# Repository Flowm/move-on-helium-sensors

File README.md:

# MOVE-ON Helium Sensors
Sensors subsystem for the MOVE-ON Helium high-altitude balloon mission.

A detailed system description can be found in .

## Interfaces
### Micro USB
The output from Micro USB can be read with the following command (MacOS):
```
picocom -b 115200 /dev/tty.usbmodem1453
```
(`usbmodem1453` needs to be adjusted on your system)

## Setup
### Requirements
- GNU Arm Embedded Toolchain
- mbed-cli
- stlink

### MacOS
```
brew cask install gcc-arm-embedded
brew install stlink openocd direnv
sudo easy_install pip
pip install virtualenv

echo 'eval "$(direnv hook bash)"' >> ~/.bashrc
echo 'eval "$(direnv hook zsh)"' >> ~/.zshrc
```

If `pip install` does not work try it with the parameter `--user python`.

### Linux
```
sudo apt install gcc-arm-none-eabi openocd
sudo apt install python-pip python-dev build-essential direnv
pip install virtualenv

echo 'eval "$(direnv hook bash)"' >> ~/.bashrc
echo 'eval "$(direnv hook zsh)"' >> ~/.zshrc
```

### Mbed-cli
New shell in project directory:
```
direnv allow
pip install mbed-cli
```

## Development
### Compile
In `src` dir:
```
make
```

### Developing in SW4STM32 (Eclipse)
1. `mbed-cli export -i sw4stm32 --profile config/develop.json`
2. `File` -> `Open Projects from File System` (In Eclipse)
3. Choose the `move-on-helium-sensors` project.
4. Remember to regenerate the project files everytime you add a new library with `mbed-cli add ...`.

## Reference
### Build targets
From the `src` directory:

| Command                 | Description                                             |
| ----------------------- | ------------------------------------------------------- |
| make build (default)    | Generate toplevel makefile and build project sources    |
| make clean              | Remove build artifacts and toplevel makefile            |
| make flash              | Upload firmware to locally attached uC with st-flash    |
| make rflash             | Upload firmware to uC attached to remote ci host        |
| make rtail              | Tail serial output from uC attached to remote ci host   |
| make deploy             | Combines rflash and rtail                               |

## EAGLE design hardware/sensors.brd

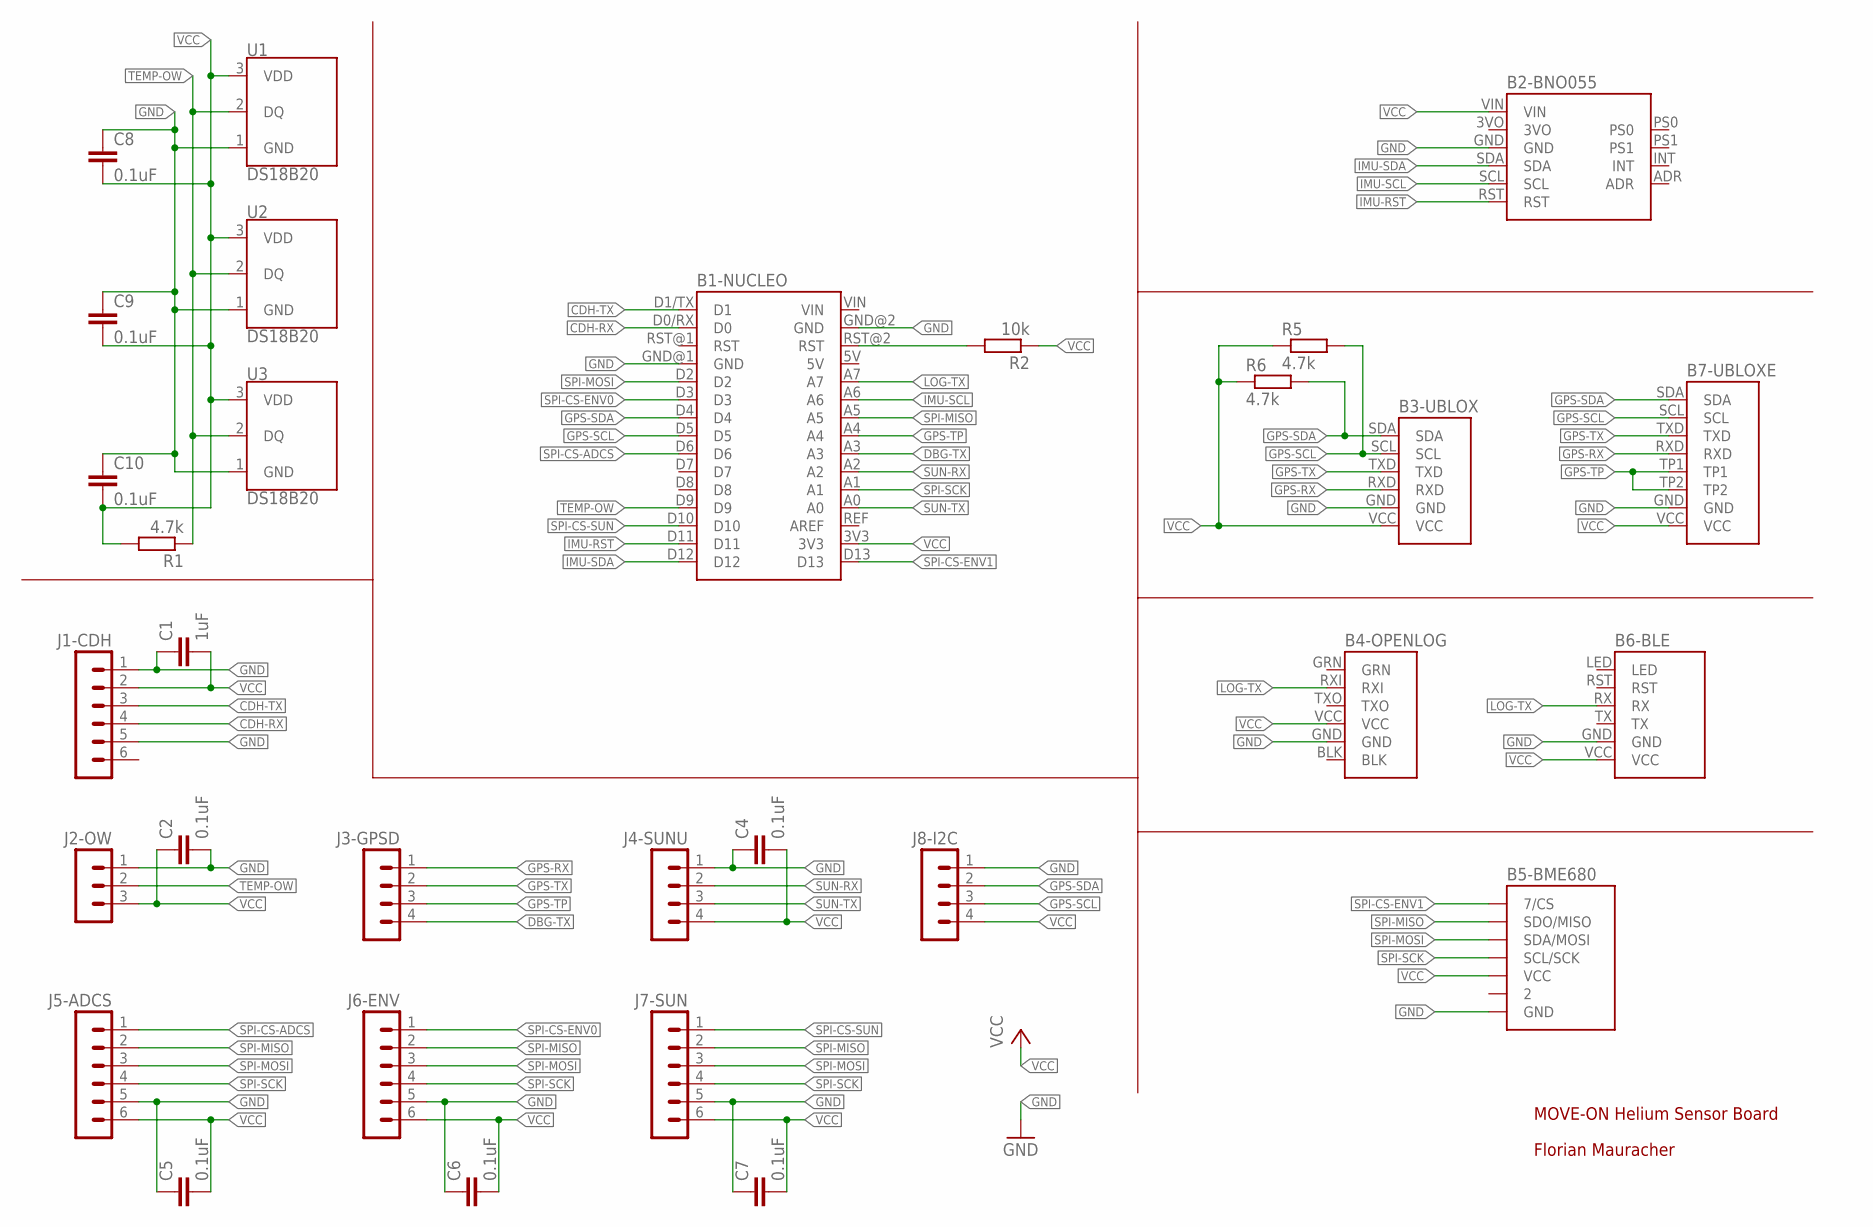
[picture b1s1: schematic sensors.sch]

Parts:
B1-NUCLEO: NUCLEO-32BO; NUCLEO-32
B2-BNO055: BOSCH-BNO055BO; BOSCH-BNO055
B3-UBLOX: UPUTRONICS-UBLOX-PICOBO; UPUTRONICS-UBLOX-PICO
B4-OPENLOG: SPARKFUN-OPENLOGBO; SPARKFUN-OPENLOG
B5-BME680: WATTEROT-BME680BO; WATTEROT-BME680
B6-BLE: HUAMAO-HM-11BO; HUAMAO-HM-11
B7-UBLOXE: UPUTRONICS-UBLOX-M8Q
C1: 1uF; C2012
C2, C4, C5, C6, C7, C8, C9, C10: 0.1uF; C2012
J1-CDH, J5-ADCS, J6-ENV, J7-SUN: 90136-106; 90136-1?06
J2-OW: 90136-103; 90136-1?03
J3-GPSD, J4-SUNU, J8-I2C: 90136-104; 90136-1?04
R1, R5, R6: 4.7k; R2012
R2: 10k; R2012
U1, U2, U3: DS18B20; TO-92-AMMO

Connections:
5V: B1-NUCLEO.5V
CDH-RX: B1-NUCLEO.D0/RX (D0), J1-CDH.4
CDH-TX: B1-NUCLEO.D1/TX (D1), J1-CDH.3
DBG-TX: B1-NUCLEO.A3, J3-GPSD.4
GND: B1-NUCLEO.GND@1 (GND), B1-NUCLEO.GND@2 (GND), B2-BNO055.GND, B3-UBLOX.GND, B4-OPENLOG.GND, B5-BME680.GND, B6-BLE.GND, B7-UBLOXE.GND, C1.1, C2.2, C4.1, C5.1, C6.1, C7.1, C8.1, C9.1, C10.1, J1-CDH.1, J1-CDH.5, J2-OW.1, J4-SUNU.1, J5-ADCS.5, J6-ENV.5, J7-SUN.5, J8-I2C.1, U1.1 (GND), U2.1 (GND), U3.1 (GND); also elsewhere on the board
GPS-RX: B3-UBLOX.RXD, B7-UBLOXE.RXD, J3-GPSD.1
GPS-SCL: B1-NUCLEO.D5, B3-UBLOX.SCL, B7-UBLOXE.SCL, J8-I2C.3, R5.2
GPS-SDA: B1-NUCLEO.D4, B3-UBLOX.SDA, B7-UBLOXE.SDA, J8-I2C.2, R6.2
GPS-TP: B1-NUCLEO.A4, B7-UBLOXE.TP1, B7-UBLOXE.TP2, J3-GPSD.3
GPS-TX: B3-UBLOX.TXD, B7-UBLOXE.TXD, J3-GPSD.2
GRN: B4-OPENLOG.GRN
IMU-RST: B1-NUCLEO.D11, B2-BNO055.RST
IMU-SCL: B1-NUCLEO.A6, B2-BNO055.SCL
IMU-SDA: B1-NUCLEO.D12, B2-BNO055.SDA
LOG-TX: B1-NUCLEO.A7, B4-OPENLOG.RXI, B6-BLE.RX
NUC-RST: B1-NUCLEO.RST@2 (RST), R2.2
SPI-CS-ADCS: B1-NUCLEO.D6, J5-ADCS.1
SPI-CS-ENV0: B1-NUCLEO.D3, J6-ENV.1
SPI-CS-ENV1: B1-NUCLEO.D13, B5-BME680.CS (7/CS)
SPI-CS-SUN: B1-NUCLEO.D10, J7-SUN.1
SPI-MISO: B1-NUCLEO.A5, B5-BME680.SDO/MISO, J5-ADCS.2, J6-ENV.2, J7-SUN.2
SPI-MOSI: B1-NUCLEO.D2, B5-BME680.SDA/MOSI, J5-ADCS.3, J6-ENV.3, J7-SUN.3
SPI-SCK: B1-NUCLEO.A1, B5-BME680.SCL/SCK, J5-ADCS.4, J6-ENV.4, J7-SUN.4
SUN-RX: B1-NUCLEO.A2, J4-SUNU.2
SUN-TX: B1-NUCLEO.A0, J4-SUNU.3
TEMP-OW: B1-NUCLEO.D9, J2-OW.2, R1.1, U1.2 (DQ), U2.2 (DQ), U3.2 (DQ)
VCC: B1-NUCLEO.3V3, B2-BNO055.VIN, B3-UBLOX.VCC, B4-OPENLOG.VCC, B5-BME680.VCC, B6-BLE.VCC, B7-UBLOXE.VCC, C1.2, C2.1, C4.2, C5.2, C6.2, C7.2, C8.2, C9.2, C10.2, J1-CDH.2, J2-OW.3, J4-SUNU.4, J5-ADCS.6, J6-ENV.6, J7-SUN.6, J8-I2C.4, R1.2, R2.1, R5.1, R6.1, U1.3 (VDD), U2.3 (VDD), U3.3 (VDD); also elsewhere on the board
VIN: B1-NUCLEO.VIN

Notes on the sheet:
MOVE-ON Helium Sensor Board
Florian Mauracher

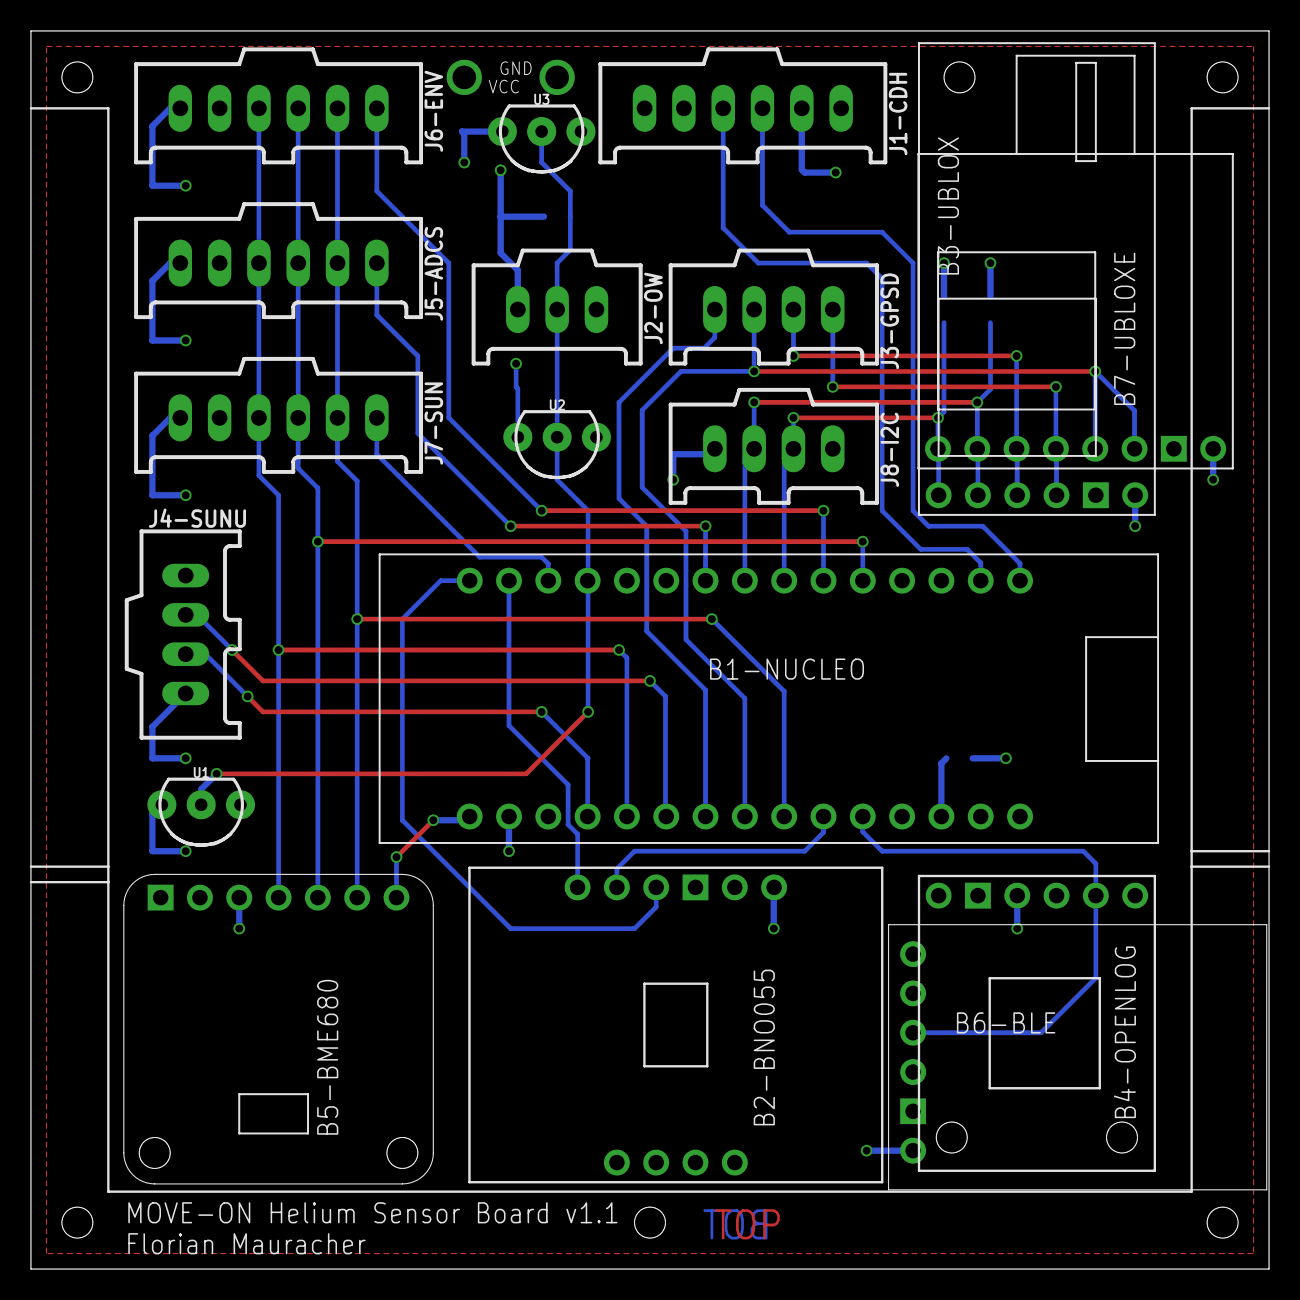
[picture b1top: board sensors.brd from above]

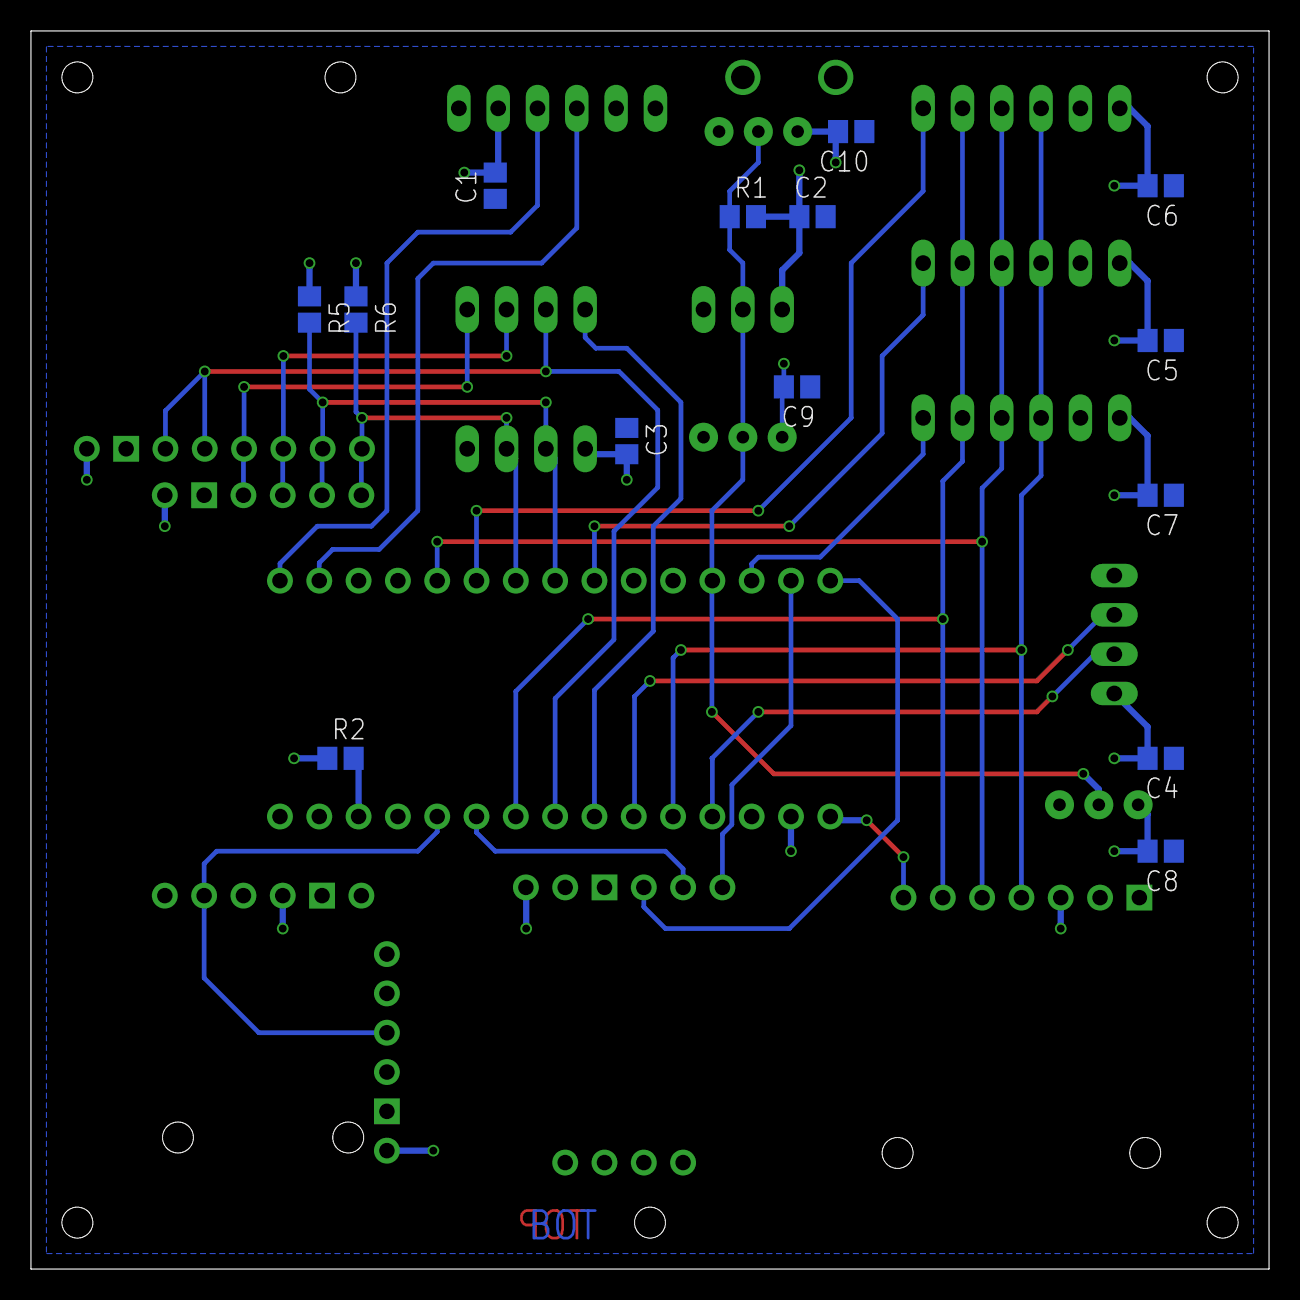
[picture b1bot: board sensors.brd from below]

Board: 2 copper layers, 80.0 x 80.0 mm, 32 parts (14 on the bottom side), 25 nets.

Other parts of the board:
C3: 0.1uF; C2012

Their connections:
GND: C3.1; also elsewhere on the board
VCC: C3.2; also elsewhere on the board

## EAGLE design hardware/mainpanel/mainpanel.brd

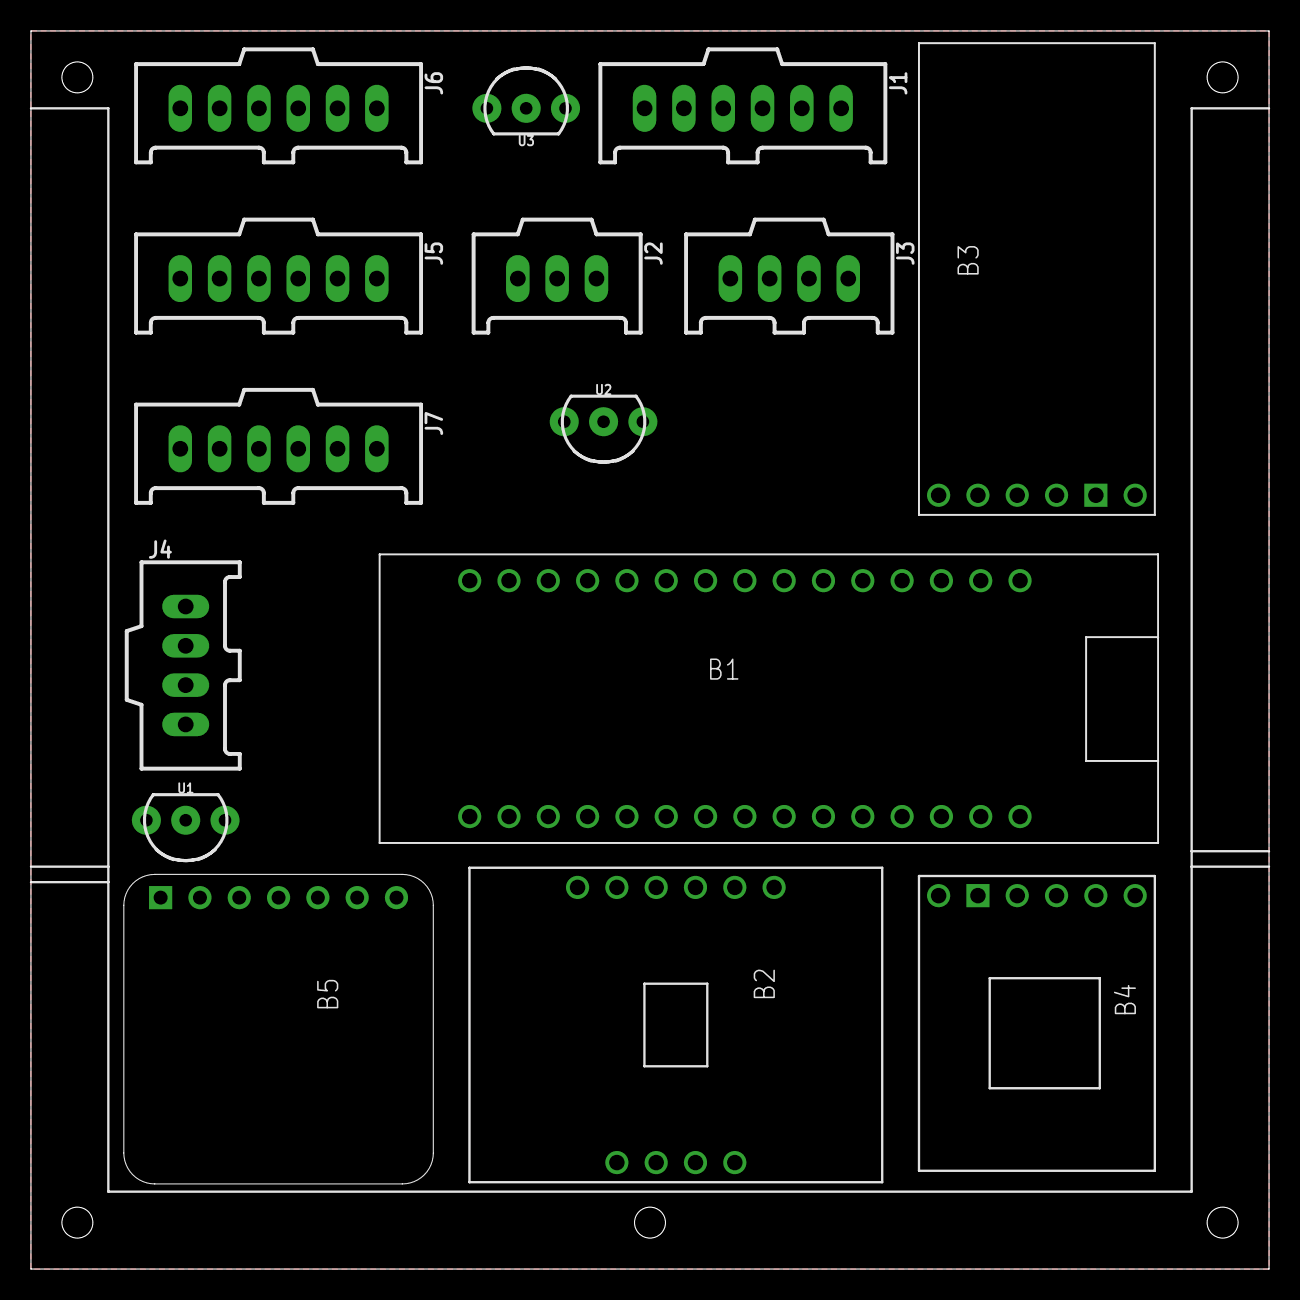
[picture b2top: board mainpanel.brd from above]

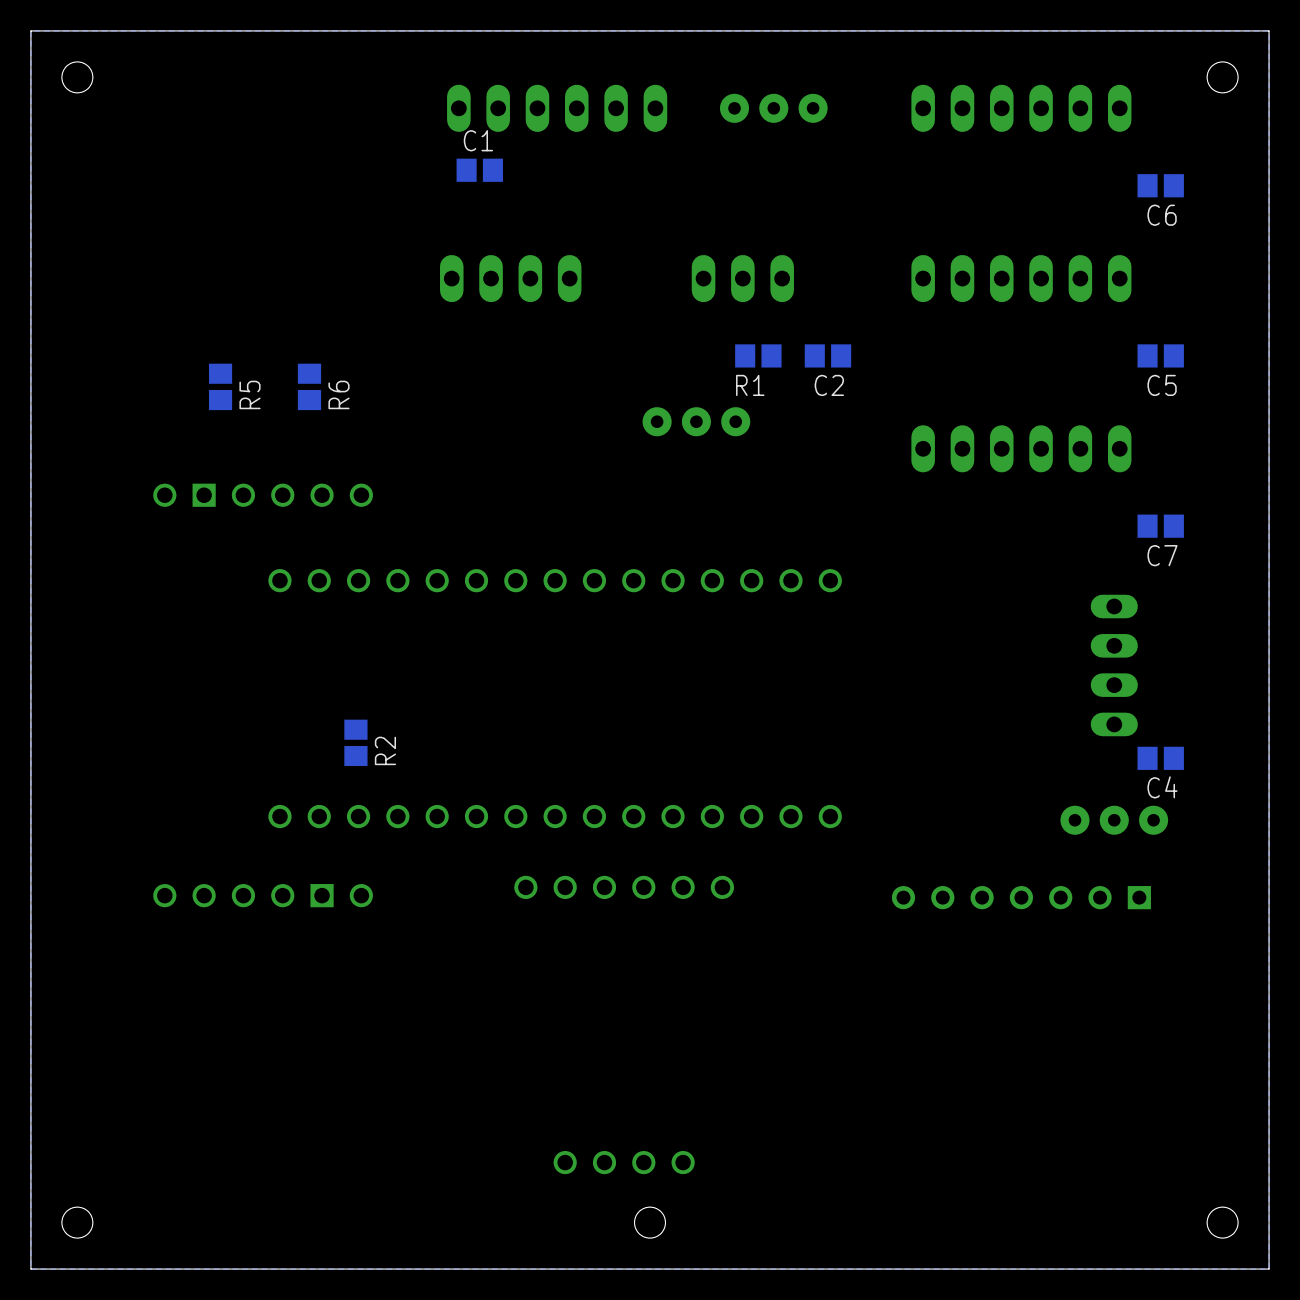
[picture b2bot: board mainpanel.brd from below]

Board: 2 copper layers, 80.0 x 80.0 mm, 25 parts (10 on the bottom side), 25 nets, no tracks yet.

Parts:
B1: NUCLEO-32
B2: BNO055; BOSCH-BNO055
B3: UBLOX; UPUTRONICS-UBLOX-PICO
B4: OPENLOG; SPARKFUN-OPENLOG
B5: BME680; WATTEROT-BME680
C1: 0.2uF; C2012
C2, C4, C5, C6, C7: 0.1uF; C2012
J1: CDH; 90136-1?06
J2: OW; 90136-1?03
J3: DBG; 90136-1?04
J4: SUN-UART; 90136-1?04
J5: ADCS; 90136-1?06
J6: ENV; 90136-1?06
J7: SUN; 90136-1?06
R1, R2, R5, R6: 4.7k; R2012
U1, U2, U3: DS18B20; TO-92-AMMO

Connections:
CDH-RX: B1.D0/RX, J1.4
CDH-TX: B1.D1/TX, J1.3
DBG-RX: B1.A4, J3.3
DBG-TX: B1.A3, J3.4
GND: B1.GND@1, B1.GND@2, B2.GND, B3.GND, B4.GND, B5.GND, C1.1, C2.1, C4.1, C5.1, C6.1, C7.1, J1.1, J1.5, J2.1, J4.1, J5.4, J6.4, J7.4, U1.1, U2.1, U3.1
GPS-RX: B3.RXD, J3.1
GPS-SCL: B1.D5, B3.SCL, R5.2
GPS-SDA: B1.D4, B3.SDA, R6.2
GPS-TX: B3.TXD, J3.2
IMU-RST: B1.D11, B2.RST
IMU-SCL: B1.A6, B2.SCL
IMU-SDA: B1.D12, B2.SDA
LOG-UART: B1.A7, B4.RXI
NUC-RST: B1.RST@2, R2.2
SPI-CS-ADCS: B1.D6, J5.1
SPI-CS-ENO: B1.D13, B5.CS
SPI-CS-ENV: B1.D3, J6.1
SPI-CS-SUN: B1.D10, J7.1
SPI-MISO: B1.A5, B5.SDO/MISO, J5.2, J6.2, J7.2
SPI-MOSI: B1.D2, B5.SDA/MOSI, J5.3, J6.3, J7.3
SPI-SCK: B1.A1, B5.SCL/SCK, J5.5, J6.5, J7.5
SUN-RX: B1.A2, J4.2
SUN-TX: B1.A0, J4.3
TEMP-OW: B1.D9, J2.2, R1.2, U1.2, U2.2, U3.2
VCC: B1.3V3, B2.VIN, B3.VCC, B4.VCC, B5.VCC, C1.2, C2.2, C4.2, C5.2, C6.2, C7.2, J1.2, J2.3, J4.4, J5.6, J6.6, J7.6, R1.1, R2.1, R5.1, R6.1, U1.3, U2.3, U3.3

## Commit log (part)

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2017-12-12 Init mbed project
2017-12-12 Add direnv and editorconfig
2017-12-12 Add basic main.cpp with pin configuration
2017-12-12 Wrap mbed build and flash in an ugly makefile
2017-12-12 Basic I2C and SPI sensor test
2017-12-14 Move port definition to sensor class
2017-12-15 Update mbed config file
2017-12-16 Implemented the MPC320X ADC Driver.
2017-12-17 Import default mbed-os build profile
2017-12-17 Switch to C++17 and C11
    Disable strict-aliasing and sized-deallocation to get rid of compiler
    warnings for mbed-os.
2017-12-20 Add circleci config
2017-12-21 Add gitlab-ci config
2017-12-21 Configure serial console with stty
2018-01-07 Explain makefile targets in readme
2018-01-07 Only install required dependencies in docker container
2018-01-12 Add basic BNO055 class testing chipid
2018-01-15 Remove unnecessary command buffer.
    Also change `rxGetLastChar()` to `getc` to prevent a buffer overflow.
2018-01-15 Update modeserial library to my repo.
    Added support for our Nucleo board. This allows for seamless setup
    of the projects for new members.
2018-01-15 Add the MODSERIAL Library to the project.
2018-01-15 Add CDH data request handling.
    Currently responds with a dummy packets with the opcode mirrorred in
    the status field.
2018-01-15 Process CDH commands in an event queue.
2018-01-15 Fix includes.
2018-01-15 Update modserial version to resolve build error.
2018-01-16 Update modserial lib to the correct HG commit.
2018-01-17 Implement BME680 sensor readout
2018-01-21 Remove sudo from pip cmd
    https://stackoverflow.com/questions/21055859/what-are-the-risks-of-running-sudo-pip
2018-01-22 Missing semicolon in the zsh/bash rc's.
2018-01-22 Fix quotations marks and redirects (to enable auto-merge)
2018-01-23 Copy data while handling CDH commands.
2018-01-23 Cleanup BME680 update func
2018-01-23 Describe bme680 thread configuration in comment
2018-01-23 Add data storage class
2018-01-23 Move BME680 lib to lib folder
2018-01-24 Only start sensor thread if sensor setup is successful
2018-01-25 Add Apache v2 LICENSE
2018-01-28 Add copying the data to the Storage
    This includes debugging output and is probably not the final version ... ;)
2018-01-28 Comment some stuff, learnt from the EPS team
2018-01-29 Remove aliases for vector attributes
    H, R, P are not necessary as aliases for X, Y, Z and are removed for clarity
2018-01-29 Remove unused variable, add implicit return to avoid compiler warning, change mapping between lib and storage
2018-01-29 Justify comment and improve formatting
2018-01-29 Make output consistent to official output
    Commented code tends to stay, or might be reused in the Sensors::log() function, so lets make it pretty.
2018-01-29 Add gyroscope and accelerometer temperatures to regular sensor readouts
2018-01-30 Add DS1820 library.
2018-01-30 Dont unlock before printing everything.
2018-01-30 Fix include.
2018-01-30 Review comments.
2018-01-30 Change DS18B20 lib to my fork. Fixes compiler warnings.
2018-01-30 WIP : Add DS1820 lib
2018-01-31 Adds Checksum class with sw and hw implementations.
    Currenntly using the software version because the hardware version
    doesnt seem to work.
2018-01-31 Influxdb line format for direct import.
2018-01-31 Add resetting sensor if selected values are zero, correct RESET pin
2018-02-01 Add mbed-cli deploy as first build step and ignore deployed libs
2018-02-01 Use mqttserial for shared serial access
2018-02-01 Wrap pyserial for serial port access
2018-02-01 Remove non-threadsafe debugging output
2018-02-01 Remove unused variables, move local variables to header file
2018-02-07 Copy datasructure to unlock it before printing over serial
2018-02-07 Move Storage and SensorThread classes to lib folder
2018-02-07 Update BME680 lib to support negative temperatures
2018-02-08 Wait for sensor threads to start and gather inital data
2018-02-14 Remove GCC version restriction.
2018-02-14 Create pinmap documenting all port assignments
2018-02-14 Implement review feedback
    - Rename bme680 chip select pin
    - Pass BNO055 reset pin from sensors class
2018-02-14 Create retention policy for influxdb
2018-02-14 Add short readme for grafana setup
2018-02-15 Add connectors
2018-02-15 Create eagle project
2018-02-15 Add DS18B20 sensors
2018-02-15 Disconnect pin 6 to cdh
2018-02-15 Add more connectors
2018-02-15 Use 0.1uF caps on all vcc/gnd lines
2018-02-15 Move parts on sch
2018-02-15 Move components
2018-02-15 Move components and add 3rd DS18B20
2018-02-15 Add brd
2018-02-15 Set rst pin to vcc
2018-02-15 Move stuff
2018-02-15 Add BNO055 and connections
2018-02-15 Remove trestrict again
2018-02-15 Implement feedback
    - BNO055 RST line
    - Del BNO055 pullups
    - 3 pin hdr for OW sensors
2018-02-15 Move some wires
2018-02-15 Switch to multi-cb dru again
2018-02-15 Add info to silkscreen
2018-02-15 Add caps for onewire sensors
2018-02-15 Update groundplane dimensions and change caps
2018-02-15 Add trestrict for autorouter
2018-02-15 Update lib
2018-02-15 Add trestrict around vcc pads for connection through cap
2018-02-15 Add power connections
2018-02-15 Update spi connectors
2018-02-15 Remove groundplane around gps
2018-02-15 Update pin names to match sw
2018-02-23 Ignore the debug directory for mbed make file generation.
    This prevents multiple inclusion errors and allows for simultaneous
    compilation with eclipse and make.
2018-02-23 Add deploy stage for rpi software
2018-02-23 Move deploy steps from makefile to gitlab ci config
2018-02-23 Add service for ser2mqttCDH.py
2018-02-23 Force reset the repo when deploying to rpi
2018-02-23 Support different topics in mqttserial
2018-02-23 Add timer to measure mutex lock delay
2018-02-23 Calculate sleep time depending on elapsed time
2018-02-23 Remove uC reset from ciflash target
2018-03-01 adapted to changes in stats output (move-on_helium 07653fc)
2018-03-01 Wrap mqtt client in MqttBroker class
2018-03-01 Added CDH grafana publish
2018-03-01 Add telegraf config for cdh and power
2018-03-01 Added ser2mqtt_power.py and moved mqtt scripts in shared dir
2018-03-01 Rename CDH topic in telegraf
2018-03-01 Mirror data to second influxdb
2018-03-01 Install nucleo reset script for every user
2018-03-01 Rename telegraf config file
2018-03-01 added eps output to ser2mqtt_cdh.py
2018-03-07 Increase baudrate of sensors serial
2018-03-07 Start with GPS Implementation.
    * Read data over I2C
    * Basic sanity checks for the data because the lenght field is not
    valid.
2018-03-07 Add note for the hack that works for reading GPS.
    Also attempt to add files to mbedignore and fail.
2018-03-07 Add a mutex to the serial class to prevent printf's getting Garbled.
    Also sets a default baudrate for the new serial class.
    Fix sentence name typo.
2018-03-07 WIP : Improvements to GPS.
2018-03-07 Update location only if we have a valid fix.
2018-03-07 Add minmea lib.
2018-03-07 Makefile hack to remove examples and test from the minmea lib.
    These files caused a compilation faliure.
2018-03-07 Parse valid time when fix is not valid yet.
2018-03-07 Use mbed lib instead of git submodule for BME680
2018-03-07 Fix build and update gitignore
2018-03-07 Change order of data prints
2018-03-08 Use adcs spi cs for env sensor testing
2018-03-08 Serialize serial access across threads
    - Use RawSerial for an interrupt safe printf implementation
    - Lock serial port manually before output
2018-03-12 Fix system stats print
2018-03-12 Add Sidepanel class
2018-03-14 Print mbed memory stats when macro is enabled in config
2018-03-14 Switch Sidepanel mode on startup
2018-03-14 Increase SPI speed
2018-03-14 Prune adcs_software datastructures
2018-03-14 Verify Sidepanel data checksum
2018-03-14 Store sidepanel data in shared structure
2018-03-14 Reset BME680 when no more data is processed
2018-03-14 Parameterize initial crc value
2018-03-14 Lock serial when warning about failed Sidepanel communication
2018-03-15 Add system architecture diagramm
2018-03-19 Add baudrate to README
2018-03-19 Comment TEMP_GYRO everywhere (Storage struct, filling, printing)
    It is still queried by the used BNO055 library though.
2018-03-20 Merge the two IMU reset types into one
    Before it was split into resets where only temperatures show invalid value (104 degrees) and where all sensors show zeroes. Now this is combined into one counter, but it can still be determined which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
2018-03-20 Make sure thread update rate is matched by deducting iteration time
2018-03-20 Add debug printf to thread sleep times
2018-03-22 Move storage and logger references to SensorThread base class
2018-03-23 Update influxdb to public url
2018-03-23 Move gps script and fix title
2018-03-23 Add print for TOSS data
2018-03-23 Implement TOSS sensor readout over spi
2018-03-23 Change comment for speed units.
2018-03-23 Parse GGA sentence for altitude.
    Also change GPS time source to GGA so that its consistent with the
    position.
2018-03-23 Implement GPS High Altitude mode configuration on boot.
2018-03-23 Retry configuration just to be sure.
2018-03-24 Add shared timer to timestamp sensor data
2018-03-24 Add sensor data print for env toss and temp
2018-03-24 Increase the delay for initial sensor thread startup
2018-03-24 Refactor prints for IMU and GPS
2018-03-24 Save sensor status information
2018-03-24 Set system status in packet header
2018-03-24 Adjust printf accurancy to sensor range
2018-03-24 Add basic c sensor parser
2018-03-24 adapted to cdh stats
2018-03-24 Add python wrapper to parse binary data from sensors
2018-03-24 Rename sensors ser2mqtt service
2018-03-24 Publish GPS data in a single measurment
2018-03-24 Move ser2mqtt helpers to lib folder
2018-03-24 Add InfluxDB user auth
2018-03-24 Update the DS18B20 library
2018-03-24 Fix number of temp sensors to 7; Change datatype to int.
    They should be interpreted as temp/100.
2018-03-24 Bruteforce Hack to fix the OW init faliure issue.
2018-03-24 Update DS1820 Library.
2018-03-24 Rename OneWire log meassages
2018-03-24 Sort GPS print and add missing separator
2018-03-25 Correctly indicate GPS status to CDH
2018-03-28 Add retries and I2C error handling for GPS.
2018-03-29 Add HBAB tracker ui
2018-03-29 Predictoion POST request WIP + Lots of formatting changes.
2018-03-29 publish cdh system status to mqtt again
2018-03-29 started to adopt input/parser/output structure for cdh debug output
2018-03-29 changed ser2mqtt_cdh.py back to use custom serial interface
2018-03-29 Add relay control scripts for EPS.
2018-03-29 Cleanup and move data processing scripts
2018-03-29 Parse TOSS data from binary data
2018-03-29 added scheduler output to ser2mqtt_cdh.py
2018-03-29 added more descriptive scheduler output
2018-03-29 Publish sensor data received over com
2018-03-29 added CDH compact stats publish to grafana
2018-03-29 Add service files for udp2mqtt_{cdh,eps}
2018-03-30 Fix negative temperature printf formatting
2018-04-03 added payload parsing
2018-04-03 Decrease TOSS update rate to 500ms as requested
2018-04-03 Add last known position and update query for faster updates.
2018-04-03 Remove unneeded code
    - Remove commented code that copies unused variables
    - Remove checking undefined variable if it is zero for resetting sensor
    - Remove commented code that could print unused variables
    - Comment unused data structs so that compiler throws error if they are still used
2018-04-03 Fix typo in comment
2018-04-03 Publish all parsed sensor data as json additionally
2018-04-03 Remove duplicate packet data from logging for better readability
2018-04-03 Drop invalid packets for sen and sengps
2018-04-04 Accept sen packets without header
2018-04-04 Fix multiple points showing up for each request to influx
2018-04-04 Add altitude calculation from density
2018-04-04 Add missing comma
2018-04-04 Use Pa instead of HPa
2018-04-04 Increase allowed invalid chunks
2018-04-09 Use argparse to specify logile
2018-04-12 Add IRR system documentation from HackMD
2018-04-12 Add Grafana screenshot with flight data
2018-05-18 Update Grafana screenshot and reference it in readme
2018-05-26 Add GPS chip with external antenna
2018-05-26 Connect external GPS chip on board
2018-05-26 Update component names
2018-05-26 Move external GPS chip
2018-05-27 Reroute I2C connections
2018-05-27 Add cap for I2C connector
2018-05-27 Add some labels
2018-05-27 Fix image links

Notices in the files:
parts and their libraries:
con-molex-c-grid: Copyright (C) 2009, Bob Starr
